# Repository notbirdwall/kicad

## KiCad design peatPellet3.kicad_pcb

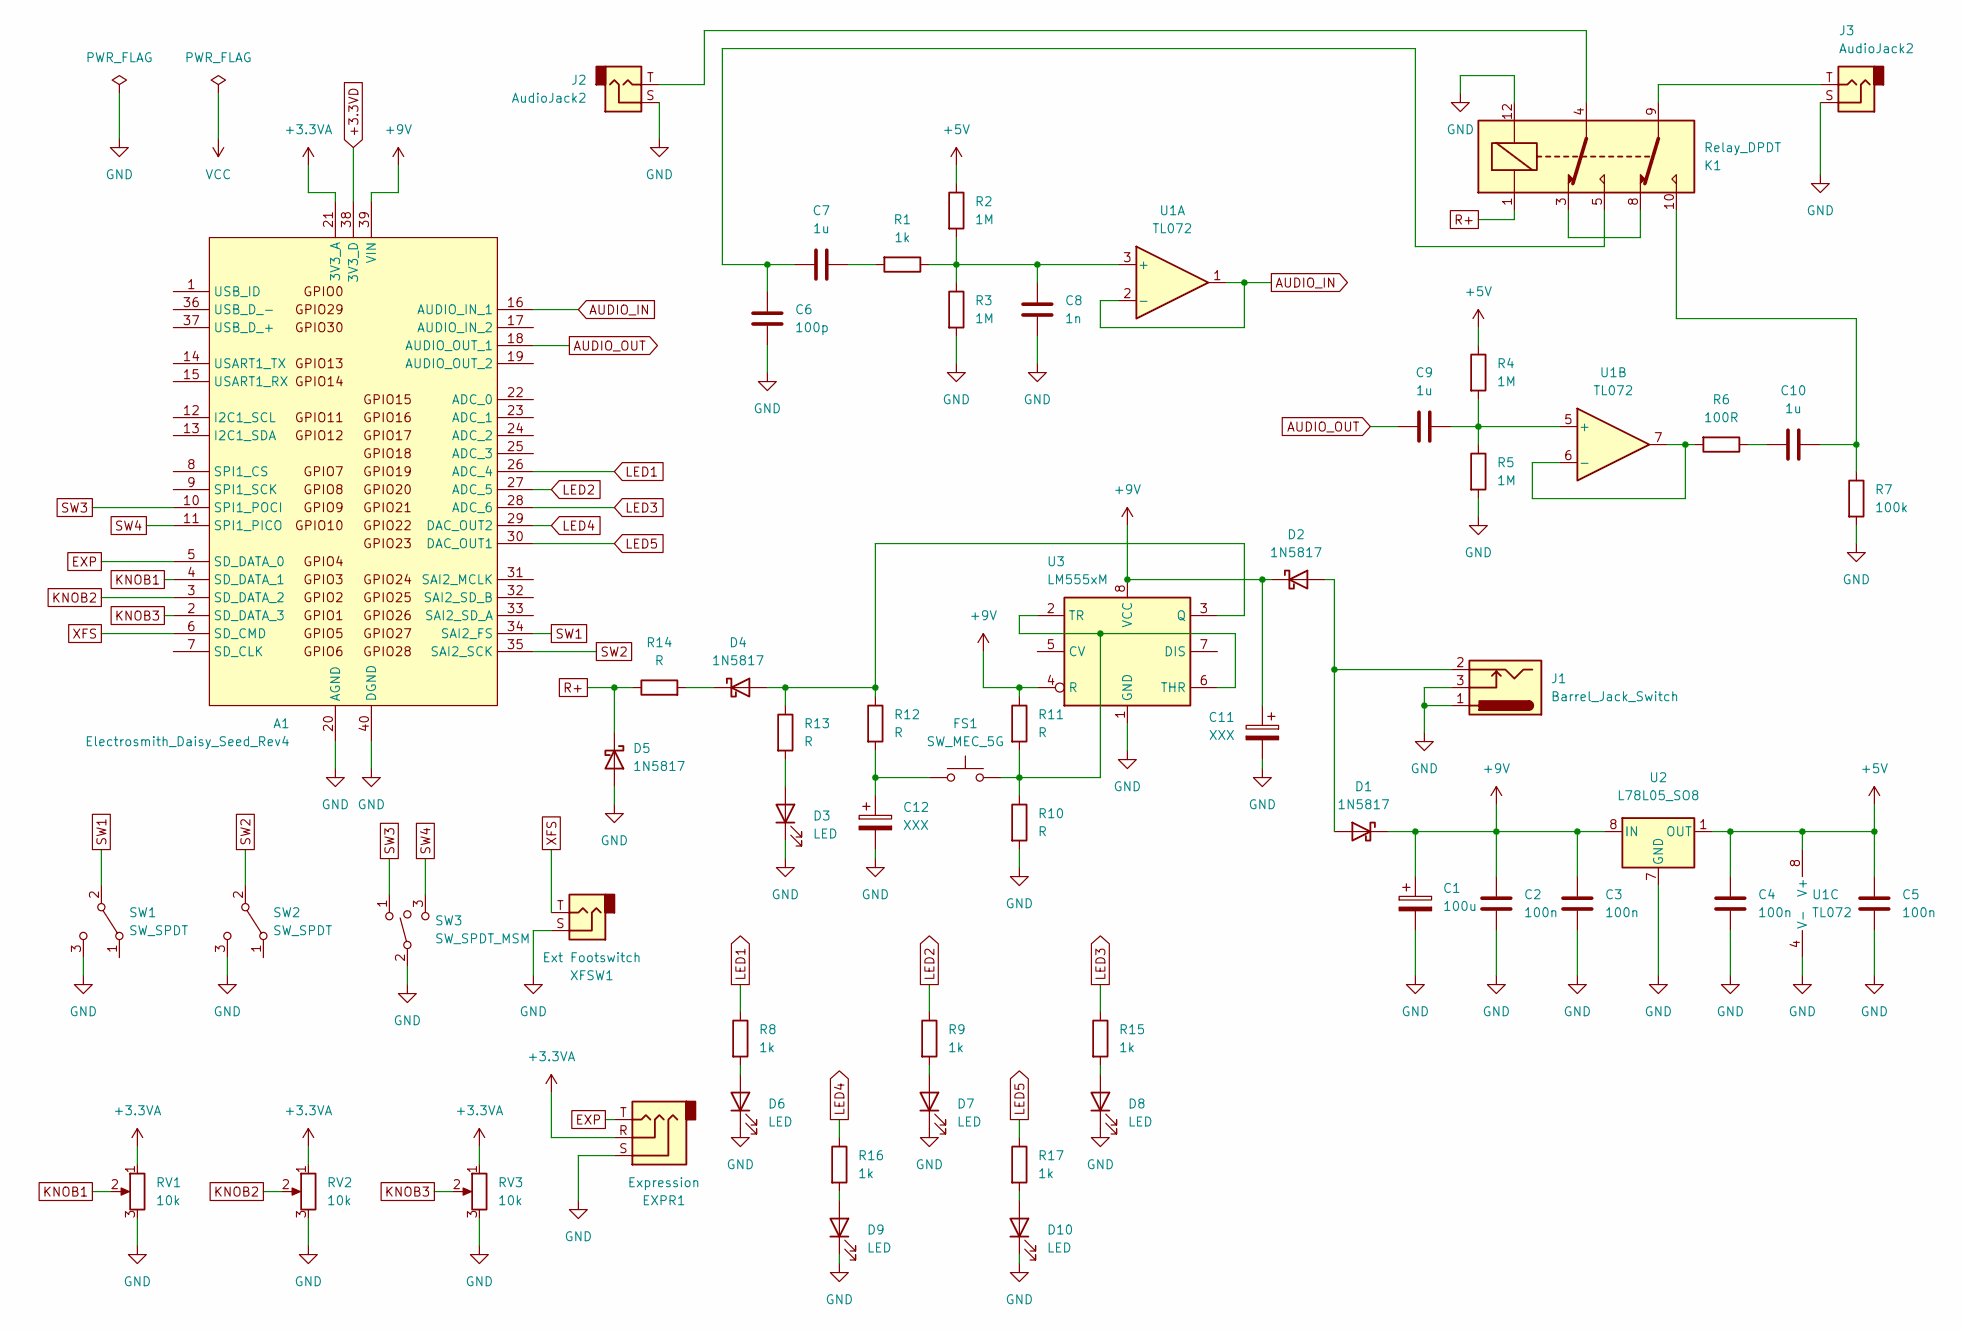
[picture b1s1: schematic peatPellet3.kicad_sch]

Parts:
A1: Electrosmith_Daisy_Seed_Rev4; Electrosmith_Daisy_Seed
C1: 100u; CP_Elec_6.3x5.4
C2, C3, C4, C5: 100n; C_0603_1608Metric
C6: 100p; C_0603_1608Metric
C7, C9, C10: 1u; C_1206_3216Metric
C8: 1n; C_0603_1608Metric
C11, C12: XXX; CP_Elec_6.3x5.4
D1, D2, D4, D5: 1N5817; D_SOD-123
D3, D6, D7, D8, D9, D10: LED; LED_D3.0mm
EXPR1: Expression; 3PADS
FS1: SW_MEC_5G; SPST.MOM
J1: Barrel_Jack_Switch; 3PADS
J2, J3: AudioJack2; 2PADS_TS
K1: Relay_DPDT; Relay_DPDT_Kemet_EE2_NU
R1, R8, R9, R15, R16, R17: 1k; R_0603_1608Metric
R2, R3, R4, R5: 1M; R_0603_1608Metric
R6: 100R; R_0603_1608Metric
R7: 100k; R_0603_1608Metric
R10, R11, R12, R13, R14: R; R_0603_1608Metric
RV1, RV2, RV3: 10k; 9MM_METAL_SHAFT
SW1, SW2: SW_SPDT; SPDT.PINS
SW3: SW_SPDT_MSM; SPDT.PINS
U1: TL072; SOIC-8_3.9x4.9mm_P1.27mm
U2: L78L05_SO8; SOIC-8_3.9x4.9mm_P1.27mm
U3: LM555xM; SOIC-8_3.9x4.9mm_P1.27mm
XFSW1: Ext Footswitch; 2PADS_TS

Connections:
+3.3VA: A1.21 (3V3_A), EXPR1.R, RV1.1, RV2.1, RV3.1
+3.3VD: A1.38 (3V3_D)
+5V: C4.1, C5.1, R2.1, R4.1, U1.8 (V+), U2.1 (OUT)
+9V: A1.39 (VIN), C1.1, C2.1, C3.1, C11.1, D1.1 (K), D2.1 (K), R11.1, U2.8 (IN), U3.4 (R), U3.8 (VCC)
AUDIO_IN: A1.16 (AUDIO_IN_1), U1.1, U1.2 (-)
AUDIO_OUT: A1.18 (AUDIO_OUT_1), C9.2
EXP: A1.5 (SD_DATA_0), EXPR1.T
GND: A1.20 (AGND), A1.40 (DGND), C1.2, C2.2, C3.2, C4.2, C5.2, C6.2, C8.2, C11.2, C12.2, D3.1 (K), D5.2 (A), D6.1 (K), D7.1 (K), D8.1 (K), D9.1 (K), D10.1 (K), EXPR1.S, J1.1, J1.3, J2.S, J3.S, K1.12, R3.2, R5.2, R7.2, R10.2, RV1.3, RV2.3, RV3.3, SW1.3 (C), SW2.3 (C), SW3.2, U1.4 (V-), U2.2 (GND), U2.3 (GND), U2.6 (GND), U2.7 (GND), U3.1 (GND), XFSW1.S
KNOB1: A1.4 (SD_DATA_1), RV1.2
KNOB2: A1.3 (SD_DATA_2), RV2.2
KNOB3: A1.2 (SD_DATA_3), RV3.2
LED1: A1.26 (ADC_4), R8.1
LED2: A1.27 (ADC_5), R9.1
LED3: A1.28 (ADC_6), R15.1
LED4: A1.29 (DAC_OUT2), R16.1
LED5: A1.30 (DAC_OUT1), R17.1
unnamed: C6.1, C7.2, K1.5
unnamed: C7.1, R1.2
unnamed: C10.1, K1.10, R7.1
unnamed: C10.2, R6.1
unnamed: C12.1, FS1.1 (A), FS1.2 (A), R12.2
unnamed: D1.2 (A), D2.2 (A), J1.2
unnamed: D3.2 (A), R13.2
unnamed: D4.2 (A), R12.1, R13.1, U3.3 (Q)
unnamed: D4.1 (K), R14.2
unnamed: D6.2 (A), R8.2
unnamed: D7.2 (A), R9.2
unnamed: D8.2 (A), R15.2
unnamed: D9.2 (A), R16.2
unnamed: D10.2 (A), R17.2
unnamed: J2.T, K1.4
unnamed: J3.T, K1.9
unnamed: K1.3, K1.8
unnamed: C8.1, R1.1, R2.2, R3.1, U1.3 (+)
unnamed: C9.1, R4.2, R5.1, U1.5 (+)
unnamed: R6.2, U1.6 (-), U1.7
unnamed: FS1.3 (B), FS1.4 (B), R10.1, R11.2, U3.2 (TR), U3.6 (THR)
R+: D5.1 (K), K1.1, R14.1
SW1: A1.34 (SAI2_FS), SW1.2 (B)
SW2: A1.35 (SAI2_SCK), SW2.2 (B)
SW3: A1.10 (SPI1_POCI), SW3.1
SW4: A1.11 (SPI1_PICO), SW3.3
XFS: A1.6 (SD_CMD), XFSW1.T

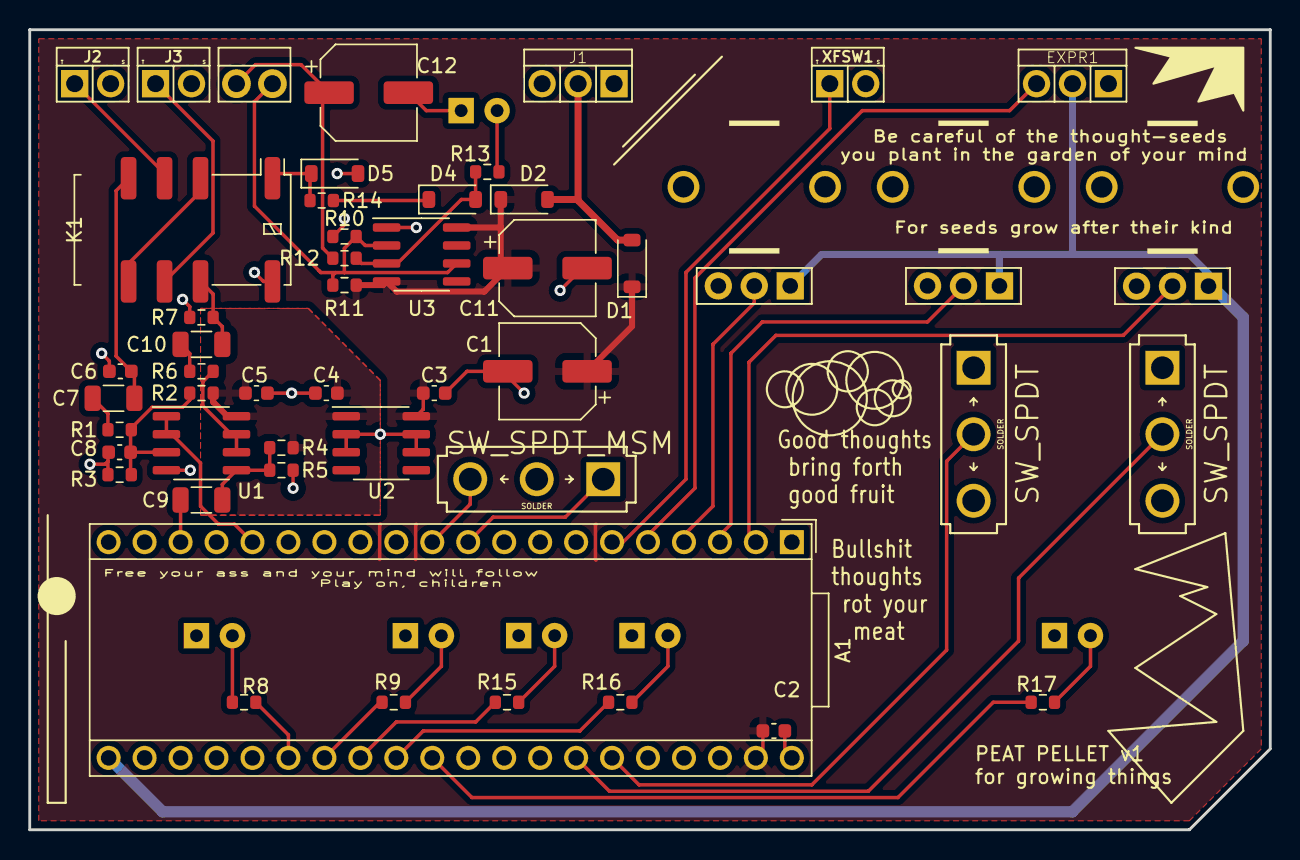
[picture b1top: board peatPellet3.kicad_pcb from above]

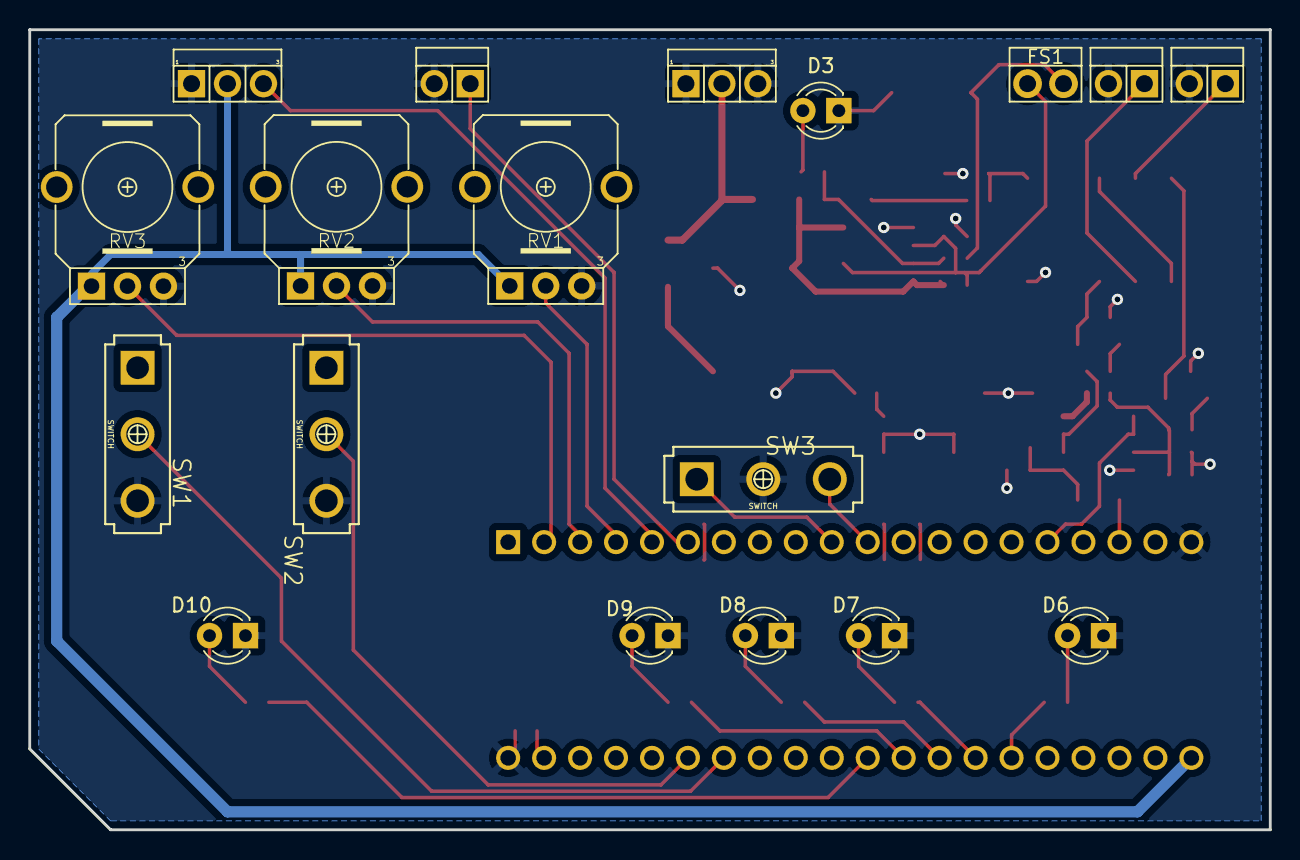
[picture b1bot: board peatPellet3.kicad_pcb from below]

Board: 2 copper layers, 87.6 x 56.5 mm, 56 parts (8 on the bottom side), 42 nets.

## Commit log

2023-08-24 first try
2023-08-24 c1 rework
2023-08-24 board outline
2023-08-24 finished wiring added pours
2023-08-24 end of 8/24
2023-08-24 seed power and 3.3v pour update
2023-08-24 fixed courtyard overlaps
2023-08-24 DRC first run through
2023-08-24 power updates: grounding, 3.3v pour
2023-08-24 via updates
2023-08-24 LED flips
2023-08-28 footprint shifts
2023-09-09 via cleanup
2023-09-09 via update 2
2023-09-09 updated pcb layou
2023-09-10 more layout updates
2023-09-10 5v pour added
2023-09-11 Last update for today, pours, zones, too much stuff to list
2023-09-18 pours, traces, graphics
2023-09-18 jumpers
2023-09-18 last for today
